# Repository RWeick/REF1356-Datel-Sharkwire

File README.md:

# REF1356-Datel-Sharkwire
Everything necessary to produce the N64 Sharkwire by Datel

This repository is the culmination of a joint effort between myself, [Jhynjhiruu](https://github.com/Jhynjhiruu), and [PPCASM](https://github.com/ppcasm). Without all of us, this wouldn't be here today. Shoutout to @WISE for being a great cheerleader throughout this endeavor. This PCB has been fully evaluated and is a complete replica of the original.

This repository now enables anyone with the necessary pcb assembly skills to fabricate an N64 Sharkwire. Some components must be harvested from an N64 Gameshark or Gameshark Pro. You are on your own to acquire the modem chipset, U11, and U13. They are COTS ICs, but seemingly hard to find. If you can find datasheets for U11 and U13, please share them with us!

Happy making!

PCB Thickness: 1.2 mm

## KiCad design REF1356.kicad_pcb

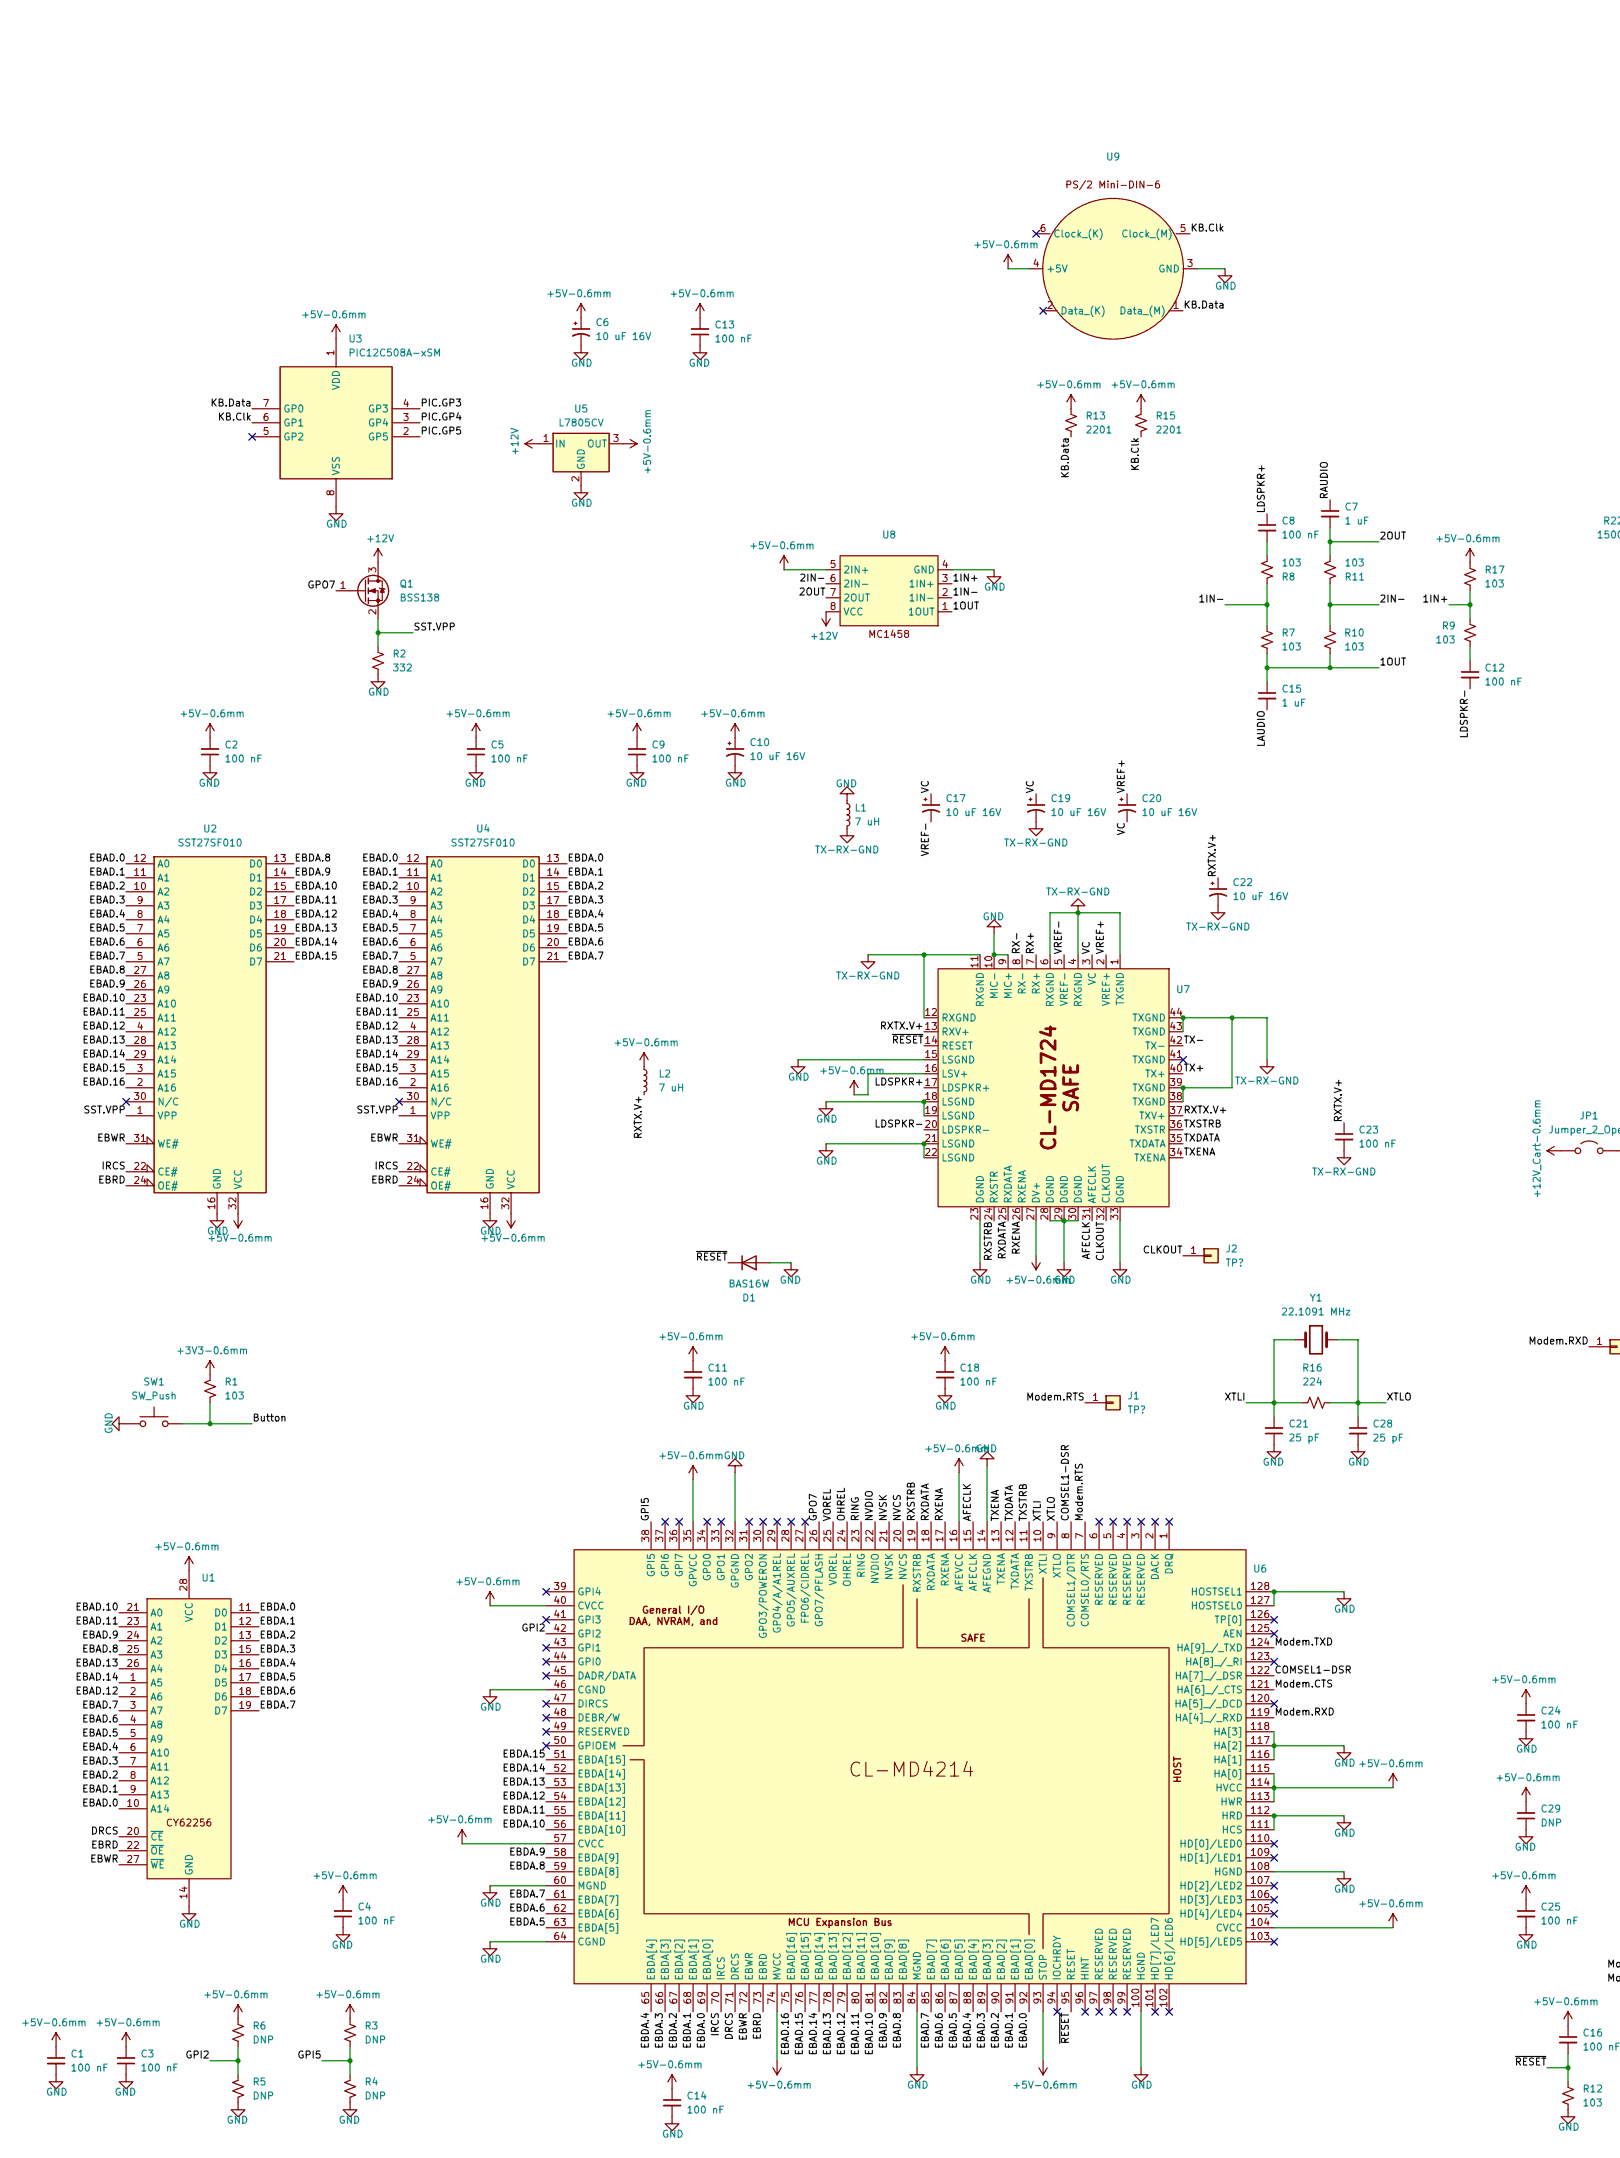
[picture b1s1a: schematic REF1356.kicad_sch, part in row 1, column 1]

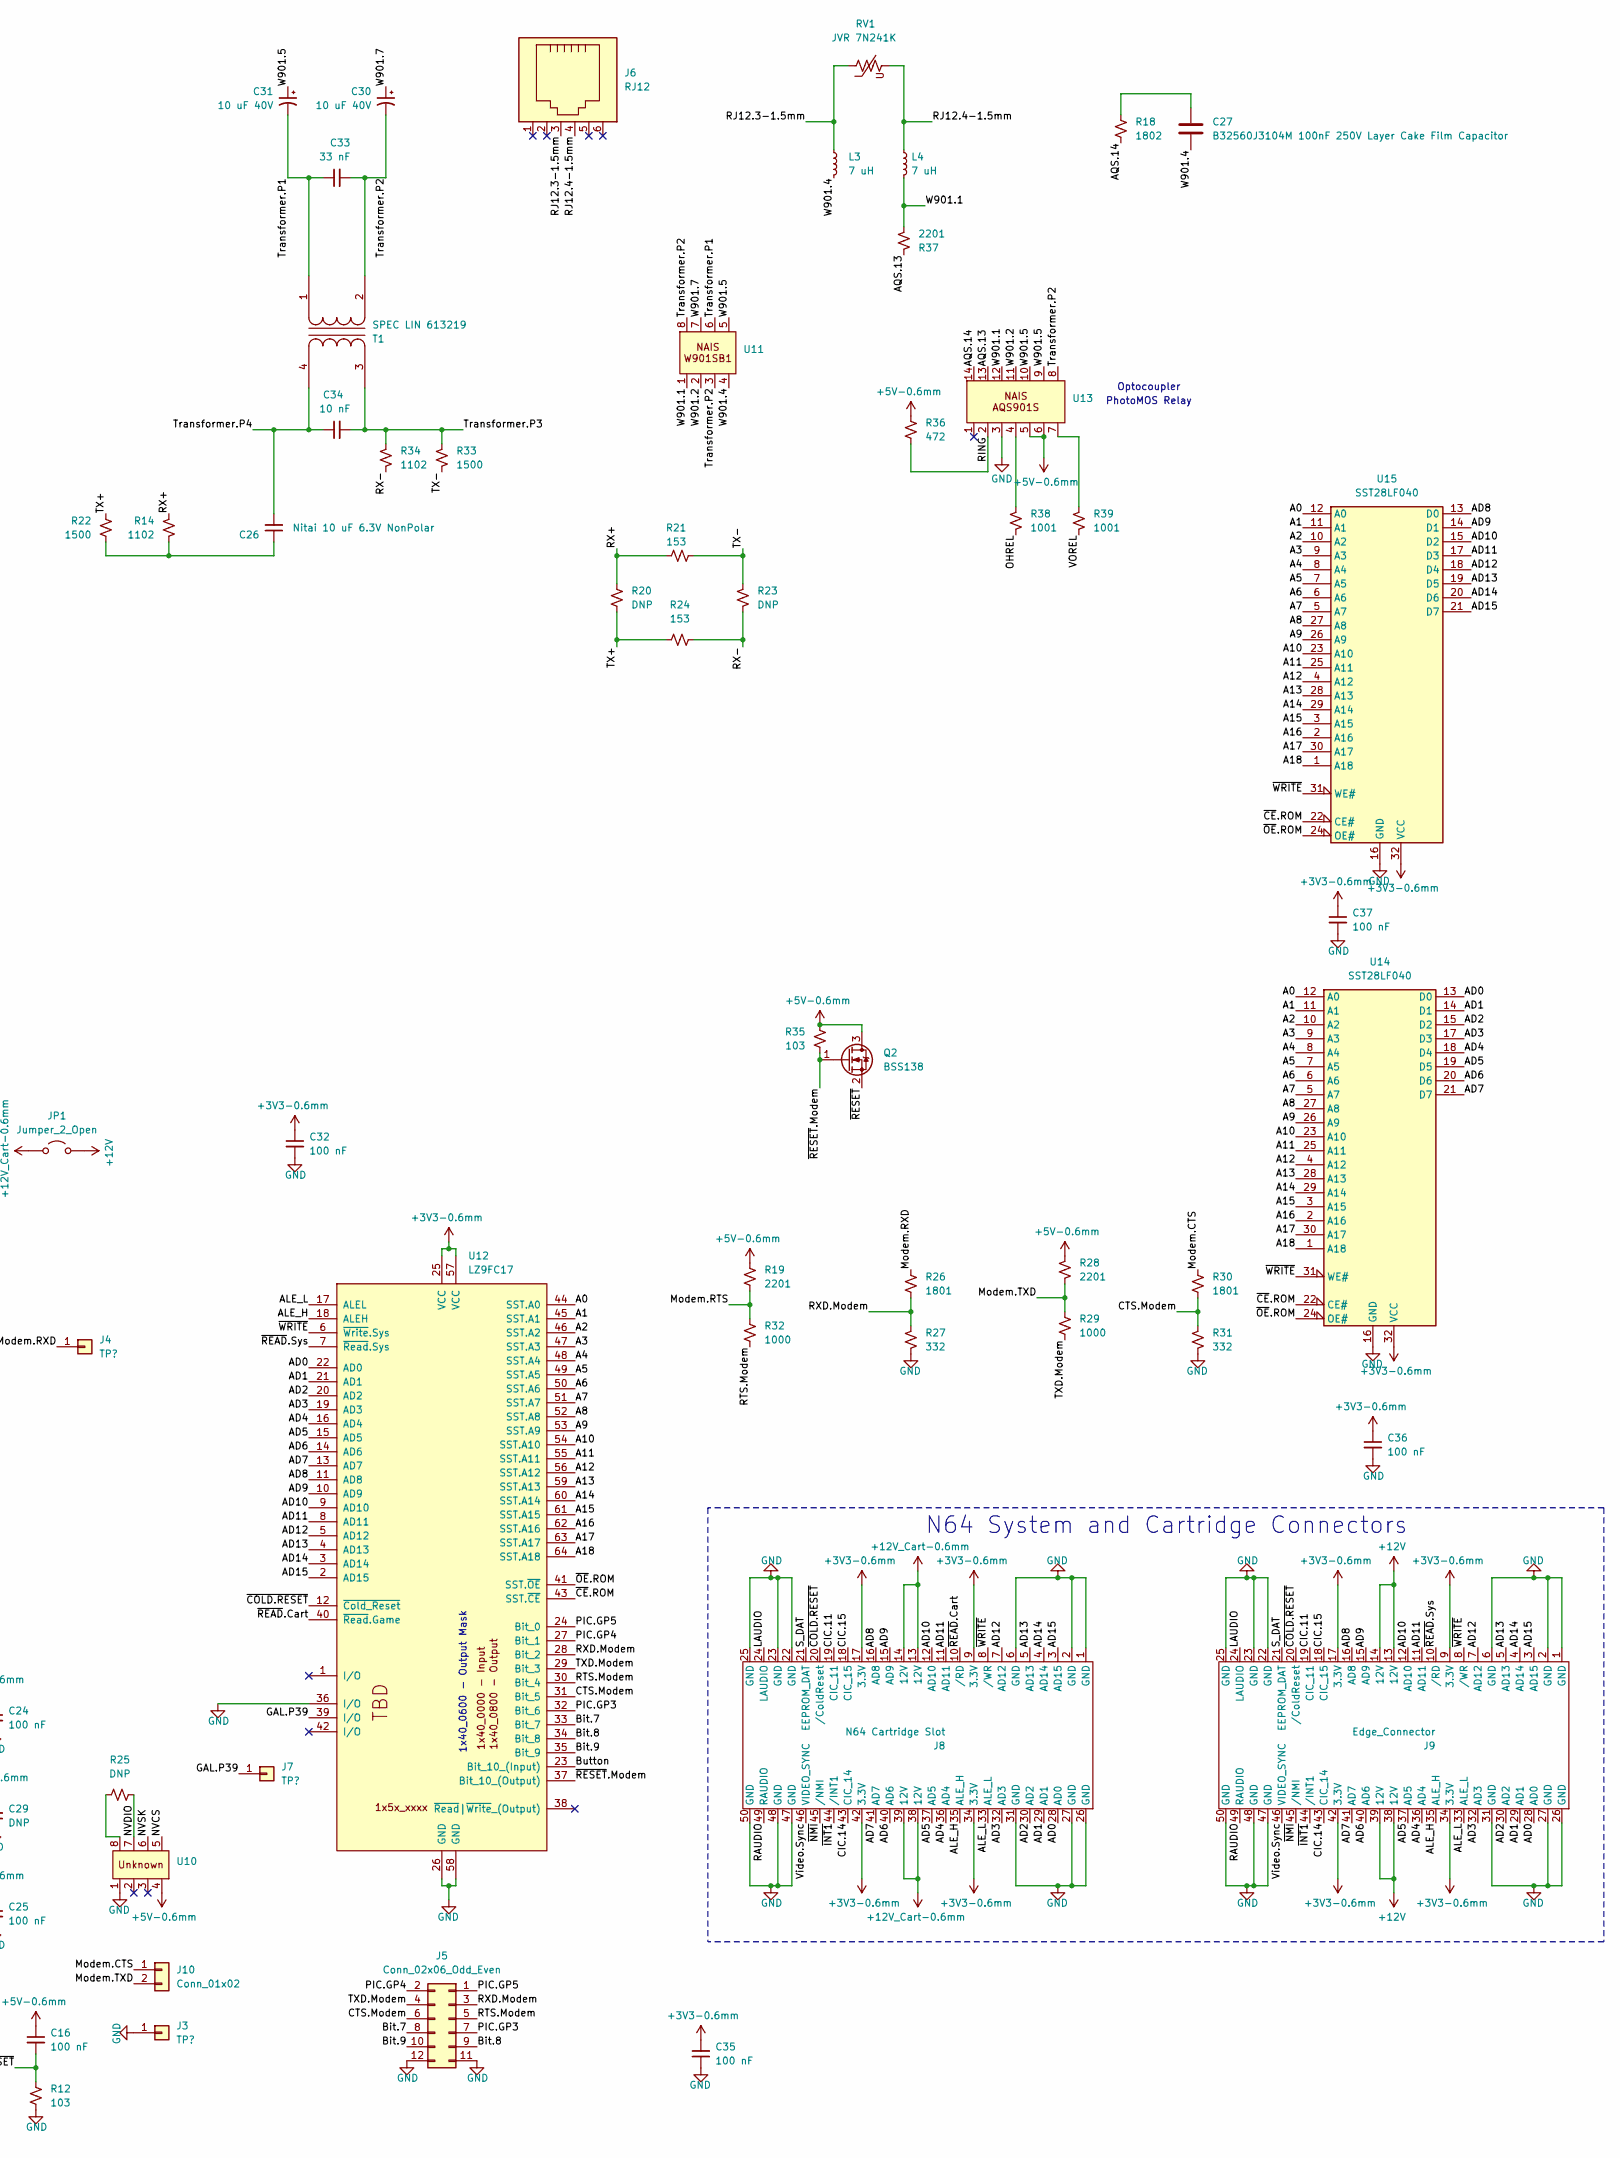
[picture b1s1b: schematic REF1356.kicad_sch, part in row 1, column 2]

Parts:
C1, C2, C3, C4, C5, C8, C9, C11, C12, C13, C14, C16, C18, C23, C24, C25, C32, C35, C36, C37: 100 nF; SMD
C6, C10, C17, C19, C20, C22: 10 uF 16V; Polar Electrolytic
C7, C15: 1 uF; SMD
C21, C28: 25 pF; SMD
C26: Nitai 10 uF 6.3V NonPolar; Nonpolar Cap
C27: B32560J3104M 100nF 250V Layer Cake Film Capacitor; Layer Cake Film Cap
C29: DNP; SMD
C30, C31: 10 uF 40V; Polar Electrolytic
C33: 33 nF; SMD
C34: 10 nF; SMD
D1: BAS16W; Transistor
J1, J2, J3, J4, J7: TP?; Test Point
J5: Conn_02x06_Odd_Even; PinHeader_2x06_P2.00mm_Vertical
J6: RJ12; Modem Jack
J8: N64 Cartridge Slot; Cartridge Slot
J9: Edge_Connector; Edge Connector
J10: Conn_01x02; Nonpolar Cap
JP1: Jumper_2_Open; 12V Jumper
L1, L2, L3, L4: 7 uH; SMD
Q1, Q2: BSS138; Transistor
R1, R7, R8, R9, R10, R11, R12, R17, R35: 103; SMD
R2, R27, R31: 332; SMD
R3, R4, R5, R6, R20, R23, R25: DNP; SMD
R13, R15, R19, R28, R37: 2201; SMD
R14, R34: 1102; SMD
R16: 224; SMD
R18: 1802; SMD
R21, R24: 153; SMD
R22, R33: 1500; SMD
R26, R30: 1801; SMD
R29, R32: 1000; SMD
R36: 472; SMD
R38, R39: 1001; SMD
RV1: JVR 7N241K; Varistor
SW1: SW_Push; Button
T1: SPEC LIN 613219
U1: CY62256-70SNC
U2, U4: SST27SF010; PLCC32
U3: PIC12C508A-xSM; PIC 12C508A
U5: L7805CV
U6: CL-MD4214-22SC-A
U7: MD1724-11VC-D
U8, U10: MC1458
U9: PS_2 Keyboard Port
U11: W901SB1
U12: LZ9FC17
U13: AQS901S
U14, U15: SST28LF040; PLCC32
Y1: 22.1091 MHz; Crystal

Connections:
+3V3-0.6mm: C32.1, C35.2, C36.1, C37.1, J8.9 (3.3V), J8.17 (3.3V), J8.34 (3.3V), J8.42 (3.3V), J9.9 (3.3V), J9.17 (3.3V), J9.34 (3.3V), J9.42 (3.3V), R1.2, U12.25 (VCC), U12.57 (VCC), U14.32 (VCC), U15.32 (VCC)
+5V-0.6mm: C1.1, C2.2, C3.2, C4.2, C5.2, C6.1, C9.2, C10.1, C11.1, C13.2, C14.1, C16.1, C18.1, C24.1, C25.1, C29.2, L2.2, Q2.3 (D), R3.1, R6.1, R13.1, R15.2, R17.1, R19.1, R28.2, R35.2, R36.1, U1.28 (VCC), U2.32 (VCC), U3.1 (VDD), U4.32 (VCC), U5.3 (OUT), U6.16 (AFEVCC), U6.35 (GPVCC), U6.40 (CVCC), U6.57 (CVCC), U6.74 (MVCC), U6.93 (STOP), U6.104 (CVCC), U6.113 (HWR), U6.114 (HVCC), U6.115 (HA[0]), U7.16 (LSV+), U7.27 (DV+), U8.5 (2IN+), U9.4 (+5V), U10.4, U13.5, U13.6
+12V: J9.13 (12V), J9.14 (12V), J9.38 (12V), J9.39 (12V), JP1.2 (B), Q1.3 (D), U5.1 (IN), U8.8 (VCC)
+12V_Cart-0.6mm: J8.13 (12V), J8.14 (12V), J8.38 (12V), J8.39 (12V), JP1.1 (A)
/1IN+: R9.2, R17.2, U8.3 (1IN+)
/1IN-: R7.1, R8.1, U8.2 (1IN-)
/1OUT: C15.1, R7.2, R10.2, U8.1 (1OUT)
/2IN-: R10.1, R11.1, U8.6 (2IN-)
/2OUT: C7.2, R11.2, U8.7 (2OUT)
/A0: U12.44 (SST.A0), U14.12 (A0), U15.12 (A0)
/A1: U12.45 (SST.A1), U14.11 (A1), U15.11 (A1)
/A2: U12.46 (SST.A2), U14.10 (A2), U15.10 (A2)
/A3: U12.47 (SST.A3), U14.9 (A3), U15.9 (A3)
/A4: U12.48 (SST.A4), U14.8 (A4), U15.8 (A4)
/A5: U12.49 (SST.A5), U14.7 (A5), U15.7 (A5)
/A6: U12.50 (SST.A6), U14.6 (A6), U15.6 (A6)
/A7: U12.51 (SST.A7), U14.5 (A7), U15.5 (A7)
/A8: U12.52 (SST.A8), U14.27 (A8), U15.27 (A8)
/A9: U12.53 (SST.A9), U14.26 (A9), U15.26 (A9)
/A10: U12.54 (SST.A10), U14.23 (A10), U15.23 (A10)
/A11: U12.55 (SST.A11), U14.25 (A11), U15.25 (A11)
/A12: U12.56 (SST.A12), U14.4 (A12), U15.4 (A12)
/A13: U12.59 (SST.A13), U14.28 (A13), U15.28 (A13)
/A14: U12.60 (SST.A14), U14.29 (A14), U15.29 (A14)
/A15: U12.61 (SST.A15), U14.3 (A15), U15.3 (A15)
/A16: U12.62 (SST.A16), U14.2 (A16), U15.2 (A16)
/A17: U12.63 (SST.A17), U14.30 (A17), U15.30 (A17)
/A18: U12.64 (SST.A18), U14.1 (A18), U15.1 (A18)
/AD0: J8.28 (AD0), J9.28 (AD0), U12.22 (AD0), U14.13 (D0)
/AD1: J8.29 (AD1), J9.29 (AD1), U12.21 (AD1), U14.14 (D1)
/AD2: J8.30 (AD2), J9.30 (AD2), U12.20 (AD2), U14.15 (D2)
/AD3: J8.32 (AD3), J9.32 (AD3), U12.19 (AD3), U14.17 (D3)
/AD4: J8.36 (AD4), J9.36 (AD4), U12.16 (AD4), U14.18 (D4)
/AD5: J8.37 (AD5), J9.37 (AD5), U12.15 (AD5), U14.19 (D5)
/AD6: J8.40 (AD6), J9.40 (AD6), U12.14 (AD6), U14.20 (D6)
/AD7: J8.41 (AD7), J9.41 (AD7), U12.13 (AD7), U14.21 (D7)
/AD8: J8.16 (AD8), J9.16 (AD8), U12.11 (AD8), U15.13 (D0)
/AD9: J8.15 (AD9), J9.15 (AD9), U12.10 (AD9), U15.14 (D1)
/AD10: J8.12 (AD10), J9.12 (AD10), U12.9 (AD10), U15.15 (D2)
/AD11: J8.11 (AD11), J9.11 (AD11), U12.8 (AD11), U15.17 (D3)
/AD12: J8.7 (AD12), J9.7 (AD12), U12.5 (AD12), U15.18 (D4)
/AD13: J8.5 (AD13), J9.5 (AD13), U12.4 (AD13), U15.19 (D5)
/AD14: J8.4 (AD14), J9.4 (AD14), U12.3 (AD14), U15.20 (D6)
/AD15: J8.3 (AD15), J9.3 (AD15), U12.2 (AD15), U15.21 (D7)
/AFECLK: U6.15 (AFECLK), U7.31 (AFECLK)
/ALE_H: J8.35 (ALE_H), J9.35 (ALE_H), U12.18 (ALEH)
/ALE_L: J8.33 (ALE_L), J9.33 (ALE_L), U12.17 (ALEL)
/AQS.13: R37.1, U13.13
/AQS.14: R18.2, U13.14
/Bit.8: J5.9, U12.34 (Bit_8)
/Bit.9: J5.10, U12.35 (Bit_9)
/Button: R1.1, SW1.2, U12.23 (Bit_10_(Input))
/CIC.11: J8.19 (CIC_11), J9.19 (CIC_11)
/CIC.14: J8.43 (CIC_14), J9.43 (CIC_14)
/CIC.15: J8.18 (CIC_15), J9.18 (CIC_15)
/CLKOUT: J2.1, U7.32 (CLKOUT)
/COMSEL1-DSR: U6.8 (COMSEL1/DTR), U6.122 (HA[7]_/_DSR)
/CTS.Modem: J5.6, R30.2, R31.2, U12.31 (Bit_5)
/DRCS: U1.20 (~CE), U6.71 (DRCS)
/EBAD.0: U1.10 (A14), U2.12 (A0), U4.12 (A0), U6.92 (EBAD[0])
/EBAD.1: U1.9 (A13), U2.11 (A1), U4.11 (A1), U6.91 (EBAD[1])
/EBAD.2: U1.8 (A12), U2.10 (A2), U4.10 (A2), U6.90 (EBAD[2])
/EBAD.3: U1.7 (A11), U2.9 (A3), U4.9 (A3), U6.89 (EBAD[3])
/EBAD.4: U1.6 (A10), U2.8 (A4), U4.8 (A4), U6.88 (EBAD[4])
/EBAD.5: U1.5 (A9), U2.7 (A5), U4.7 (A5), U6.87 (EBAD[5])
/EBAD.6: U1.4 (A8), U2.6 (A6), U4.6 (A6), U6.86 (EBAD[6])
/EBAD.7: U1.3 (A7), U2.5 (A7), U4.5 (A7), U6.85 (EBAD[7])
/EBAD.8: U1.25 (A3), U2.27 (A8), U4.27 (A8), U6.83 (EBAD[8])
/EBAD.9: U1.24 (A2), U2.26 (A9), U4.26 (A9), U6.82 (EBAD[9])
/EBAD.10: U1.21 (A0), U2.23 (A10), U4.23 (A10), U6.81 (EBAD[10])
/EBAD.11: U1.23 (A1), U2.25 (A11), U4.25 (A11), U6.80 (EBAD[11])
/EBAD.12: U1.2 (A6), U2.4 (A12), U4.4 (A12), U6.79 (EBAD[12])
/EBAD.13: U1.26 (A4), U2.28 (A13), U4.28 (A13), U6.78 (EBAD[13])
/EBAD.14: U1.1 (A5), U2.29 (A14), U4.29 (A14), U6.77 (EBAD[14])
/EBAD.15: U2.3 (A15), U4.3 (A15), U6.76 (EBAD[15])
/EBAD.16: U2.2 (A16), U4.2 (A16), U6.75 (EBAD[16])
/EBDA.0: U1.11 (D0), U4.13 (D0), U6.69 (EBDA[0])
/EBDA.1: U1.12 (D1), U4.14 (D1), U6.68 (EBDA[1])
/EBDA.2: U1.13 (D2), U4.15 (D2), U6.67 (EBDA[2])
/EBDA.3: U1.15 (D3), U4.17 (D3), U6.66 (EBDA[3])
/EBDA.4: U1.16 (D4), U4.18 (D4), U6.65 (EBDA[4])
/EBDA.5: U1.17 (D5), U4.19 (D5), U6.63 (EBDA[5])
/EBDA.6: U1.18 (D6), U4.20 (D6), U6.62 (EBDA[6])
/EBDA.7: U1.19 (D7), U4.21 (D7), U6.61 (EBDA[7])
/EBDA.8: U2.13 (D0), U6.59 (EBDA[8])
/EBDA.9: U2.14 (D1), U6.58 (EBDA[9])
/EBDA.10: U2.15 (D2), U6.56 (EBDA[10])
/EBDA.11: U2.17 (D3), U6.55 (EBDA[11])
/EBDA.12: U2.18 (D4), U6.54 (EBDA[12])
/EBDA.13: U2.19 (D5), U6.53 (EBDA[13])
/EBDA.14: U2.20 (D6), U6.52 (EBDA[14])
/EBDA.15: U2.21 (D7), U6.51 (EBDA[15])
/EBRD: U1.22 (~OE), U2.24 (OE#), U4.24 (OE#), U6.73 (EBRD)
/EBWR: U1.27 (~WE), U2.31 (WE#), U4.31 (WE#), U6.72 (EBWR)
/GAL.P33: J5.8, U12.33 (I/O)
/GAL.P39: J7.1, U12.39 (I/O)
/GPI2: R5.2, R6.2, U6.42 (GPI2)
/GPI5: R3.2, R4.2, U6.38 (GPI5)
/GPO7: Q1.1 (G), U6.26 (GPO7/PFLASH)
/IRCS: U2.22 (CE#), U4.22 (CE#), U6.70 (IRCS)
/KB.Clk: R15.1, U3.6 (GP1), U9.5 (Clock_(M))
/KB.Data: R13.2, U3.7 (GP0), U9.1 (Data_(M))
/LAUDIO: C15.2, J8.24 (LAUDIO), J9.24 (LAUDIO)
/LDSPKR+: C8.1, U7.17 (LDSPKR+)
/LDSPKR-: C12.2, U7.20 (LDSPKR-)
/Modem.CTS: J10.1, R30.1, U6.121 (HA[6]_/_CTS)
/Modem.RTS: J1.1, R19.2, R32.1, U6.7 (COMSEL0/RTS)
/Modem.RXD: J4.1, R26.1, U6.119 (HA[4]_/_RXD)
/Modem.TXD: J10.2, R28.1, R29.1, U6.124 (HA[9]_/_TXD)
/NVCS: U6.20 (NVCS), U10.5
/NVDIO: R25.2, U6.22 (NVDIO), U10.7
/NVSK: U6.21 (NVSK), U10.6
/OHREL: R38.1, U6.24 (OHREL)
/PIC.GP3: J5.7, U3.4 (GP3), U12.32 (Bit_6)
/PIC.GP4: J5.2, U3.3 (GP4), U12.27 (Bit_1)
/PIC.GP5: J5.1, U3.2 (GP5), U12.24 (Bit_0)
/RAUDIO: C7.1, J8.49 (RAUDIO), J9.49 (RAUDIO)
/RING: R36.2, U6.23 (RING), U13.2
/RJ12.3-1.5mm: J6.3, L3.2, RV1.1
/RJ12.4-1.5mm: J6.4, L4.1, RV1.2
/RTS.Modem: J5.5, R32.2, U12.30 (Bit_4)
/RX+: R14.1, R20.1, R21.1, U7.7 (RX+)
/RX-: R23.1, R24.2, R34.1, U7.8 (RX-)
/RXD.Modem: J5.3, R26.2, R27.2, U12.28 (Bit_2)
/RXDATA: U6.18 (RXDATA), U7.25 (RXDATA)
/RXENA: U6.17 (RXENA), U7.26 (RXENA)
/RXSTRB: U6.19 (RXSTRB), U7.24 (RXSTR)
/RXTX.V+: C22.1, C23.1, L2.1, U7.13 (RXV+), U7.37 (TXV+)
/SST.VPP: Q1.2 (S), R2.1, U2.1 (VPP), U4.1 (VPP)
/S_DAT: J8.21 (EEPROM_DAT), J9.21 (EEPROM_DAT)
/TX+: R20.2, R22.2, R24.1, U7.40 (TX+)
/TX-: R21.2, R23.2, R33.1, U7.42 (TX-)
/TXD.Modem: J5.4, R29.2, U12.29 (Bit_3)
/TXDATA: U6.12 (TXDATA), U7.35 (TXDATA)
/TXENA: U6.13 (TXENA), U7.34 (TXENA)
/TXSTRB: U6.11 (TXSTRB), U7.36 (TXSTR)
/Transformer.P1: C31.2, C33.1, T1.1 (AA), U11.6
/Transformer.P2: C30.2, C33.2, T1.2 (AB), U11.3, U11.8, U13.8
/Transformer.P3: C34.2, R33.2, R34.2, T1.3 (SA)
/Transformer.P4: C26.2, C34.1, T1.4 (SB)
/VC: C17.1, C19.1, C20.2, U7.3 (VC)
/VOREL: R39.1, U6.25 (VOREL)
/VREF+: C20.1, U7.2 (VREF+)
/VREF-: C17.2, U7.5 (VREF-)
/Video.Sync: J8.46 (VIDEO_SYNC), J9.46 (VIDEO_SYNC)
/W901.1: L4.2, R37.2, U11.1, U13.12
/W901.2: U11.2, U13.11
/W901.4: C27.2, L3.1, U11.4
/W901.5: C31.1, U11.5, U13.9, U13.10
/W901.7: C30.1, U11.7
/XTLI: C21.2, R16.1, U6.10 (XTLI), Y1.1
/XTLO: C28.1, R16.2, U6.9 (XTLO), Y1.2
/~CE.ROM: U12.43 (SST.~CE), U14.22 (CE#), U15.22 (CE#)
/~COLD.RESET: J8.20 (/ColdReset), J9.20 (/ColdReset), U12.12 (~Cold_Reset)
/~INT1: J8.44 (/INT1), J9.44 (/INT1)
/~NMI: J8.45 (/NMI), J9.45 (/NMI)
/~OE.ROM: U12.41 (SST.~OE), U14.24 (OE#), U15.24 (OE#)
/~READ.Cart: J8.10 (/RD), U12.40 (~Read.Game)
/~READ.Sys: J9.10 (/RD), U12.7 (~Read.Sys)
/~RESET: C16.2, D1.3 (K), Q2.2 (S), R12.1, U6.95 (RESET), U7.14 (RESET)
/~RESET.Modem: Q2.1 (G), R35.1, U12.37 (Bit_10_(Output))
/~WRITE: J8.8 (/WR), J9.8 (/WR), U12.6 (~Write.Sys), U14.31 (WE#), U15.31 (WE#)
GND: C1.2, C2.1, C3.1, C4.1, C5.1, C6.2, C9.1, C10.2, C11.2, C13.1, C14.2, C18.2, C21.1, C24.2, C25.2, C28.2, C29.1, C32.2, C35.1, C36.2, C37.2, D1.1 (A), J3.1, J5.11, J5.12, J8.1 (GND), J8.2 (GND), J8.6 (GND), J8.22 (GND), J8.23 (GND), J8.25 (GND), J8.26 (GND), J8.27 (GND), J8.31 (GND), J8.47 (GND), J8.48 (GND), J8.50 (GND), J9.1 (GND), J9.2 (GND), J9.6 (GND), J9.22 (GND), J9.23 (GND), J9.25 (GND), J9.26 (GND), J9.27 (GND), J9.31 (GND), J9.47 (GND), J9.48 (GND), J9.50 (GND), L1.1, R2.2, R4.1, R5.1, R12.2, R27.1, R31.1, SW1.1, U1.14 (GND), U2.16 (GND), U3.8 (VSS), U4.16 (GND), U5.2 (GND), U6.14 (AFEGND), U6.32 (GPGND), U6.46 (CGND), U6.60 (MGND), U6.64 (CGND), U6.84 (MGND), U6.100 (HGND), U6.108 (HGND), U6.111 (HCS), U6.112 (HRD), U6.116 (HA[1]), U6.117 (HA[2]), U6.118 (HA[3]), U6.127 (HOSTSEL0), U6.128 (HOSTSEL1), U7.9 (MIC+), U7.10 (MIC-), U7.15 (LSGND), U7.18 (LSGND), U7.19 (LSGND), U7.21 (LSGND), U7.22 (LSGND), U7.23 (DGND), U7.28 (DGND), U7.29 (DGND), U7.30 (DGND), U7.33 (DGND), U8.4 (GND), U9.3 (GND), U10.1, U12.26 (GND), U12.36 (I/O), U12.58 (GND), U13.3, U14.16 (GND), U15.16 (GND)
unnamed: C8.2, R8.2
unnamed: C12.1, R9.1
unnamed: C26.1, R14.2, R22.1
unnamed: C27.1, R18.1
unnamed: R25.1, U10.8
unnamed: R38.2, U13.4
unnamed: R39.2, U13.7
TX-RX-GND: C19.2, C22.2, C23.2, L1.2, U7.1 (TXGND), U7.4 (RXGND), U7.6 (RXGND), U7.11 (RXGND), U7.12 (RXGND), U7.38 (TXGND), U7.39 (TXGND), U7.43 (TXGND), U7.44 (TXGND)

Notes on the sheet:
Optocoupler
PhotoMOS Relay
1x40_0600 - Output Mask
N64 System and Cartridge Connectors

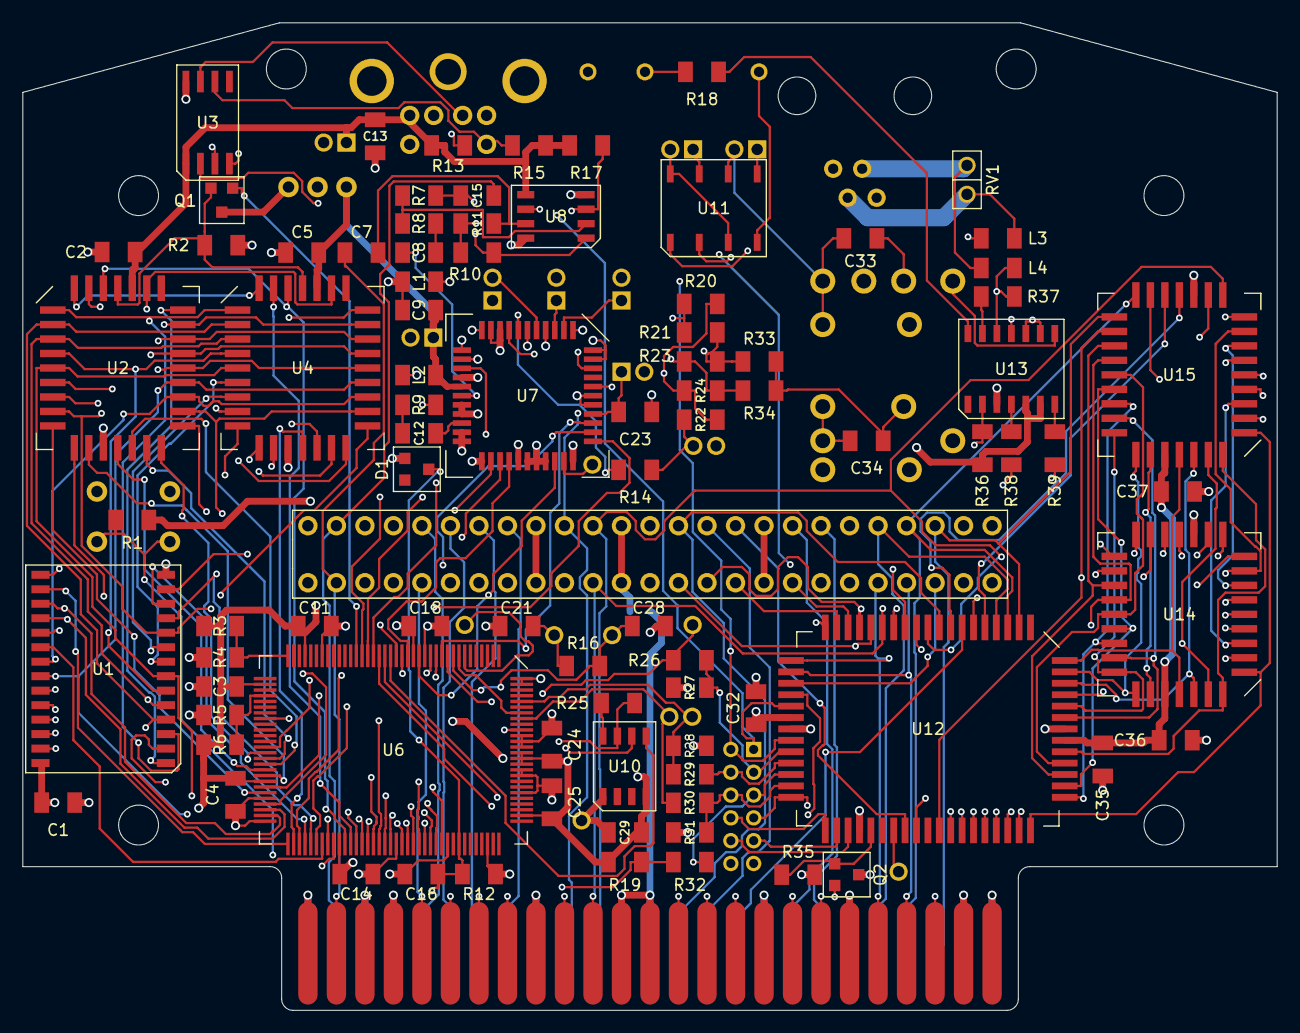
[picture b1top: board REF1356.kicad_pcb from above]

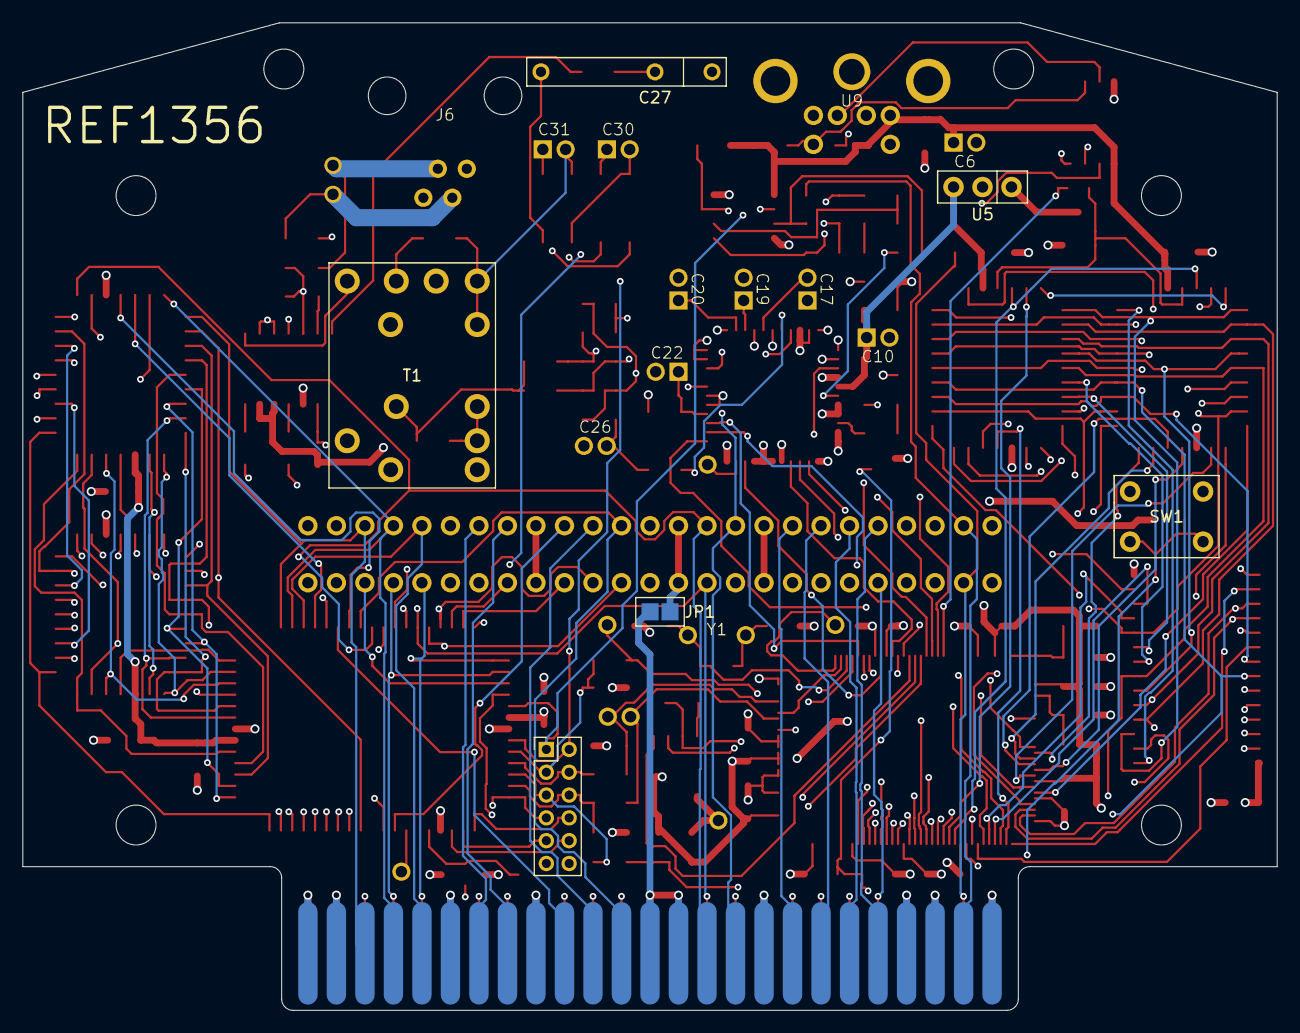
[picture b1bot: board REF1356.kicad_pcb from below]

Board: 4 copper layers, 110.0 x 86.6 mm, 113 parts (3 on the bottom side), 171 nets.
